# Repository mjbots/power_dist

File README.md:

# mjbots power_dist and mjpower-ss #

This repository contains hardware and firmware for the mjbots
power_dist and mjpower-ss boards.  Both provide pre-charge,
over-current limiting and connector fanout.  The power_dist
additionally provides energy monitoring and a soft-switch
functionality.

# Specifications #

| Name                     | power_dist r4.5b | mjpower-ss r2 |
| ------------------------ |------------------|---------------|
| Voltage Input            | 10-44V           | 10-54V        |
| Current (continous/peak) | 45A/90A          | 45/90A        |
| Output                   | 6x XT30          | 6x XT30       |
| Max load capacitance     | 4000uF           | 4000uF        |
| Quiescent current        | 300uA            | 200uA         |
| Dimensions               | 80x50mm          | 70x50mm       |
| Mass                     | 36g              | 34g           |
| External switch          | X                | X             |
| Soft switch              | X                |               |
| Onboard switch           |                  | X             |
| CAN communication        | X                |               |

# Documentation #

* [Reference](docs/reference.md)

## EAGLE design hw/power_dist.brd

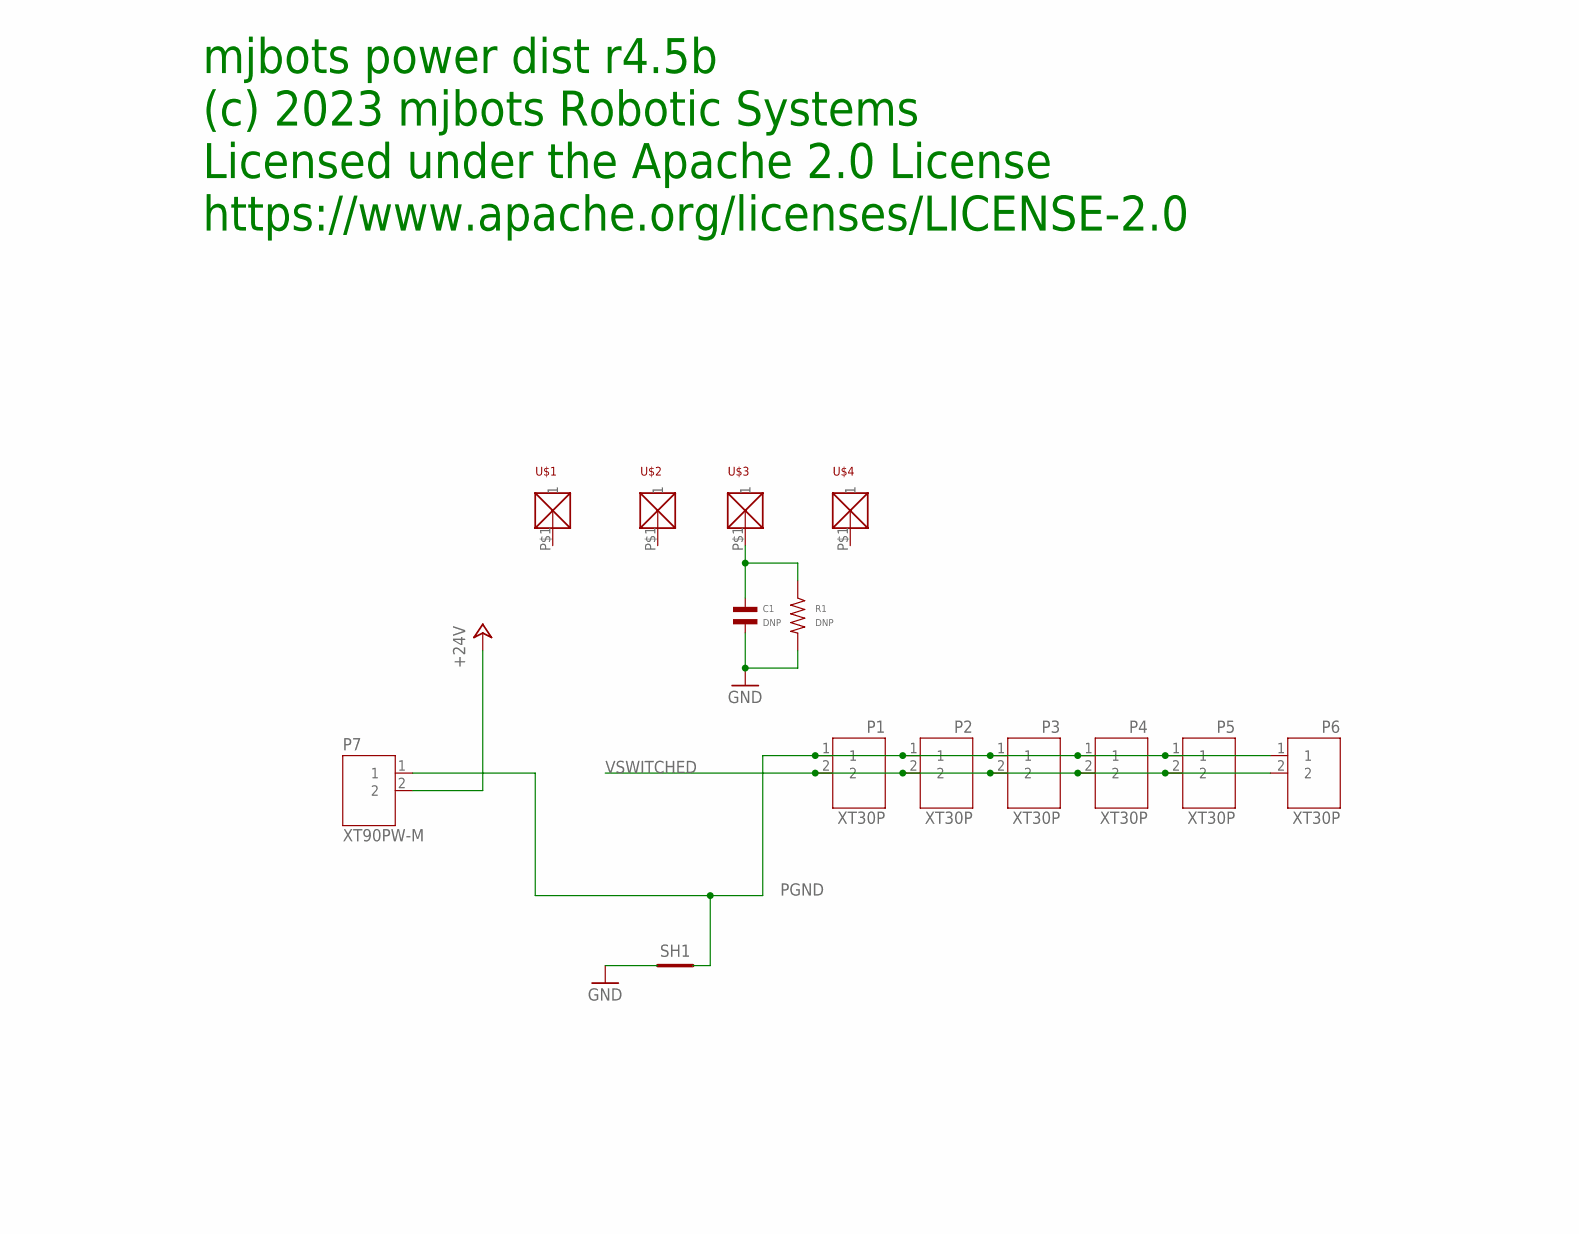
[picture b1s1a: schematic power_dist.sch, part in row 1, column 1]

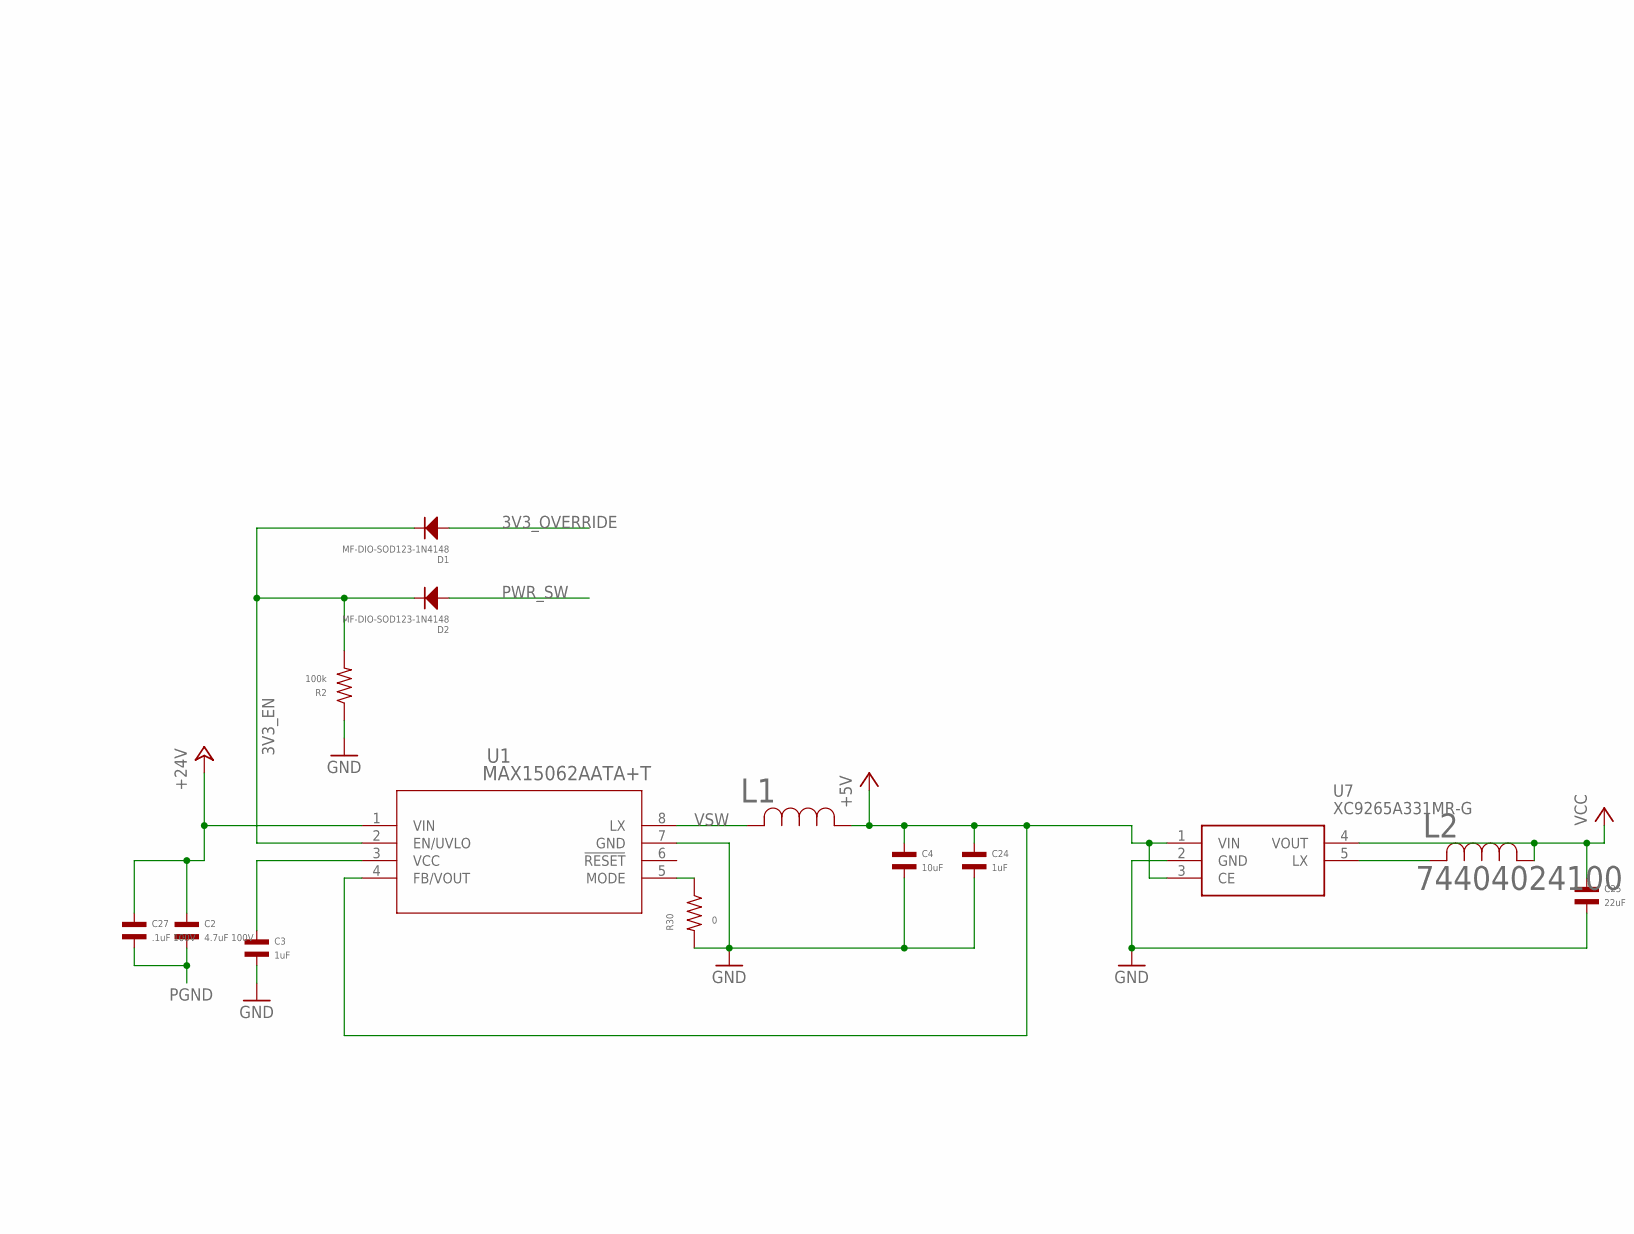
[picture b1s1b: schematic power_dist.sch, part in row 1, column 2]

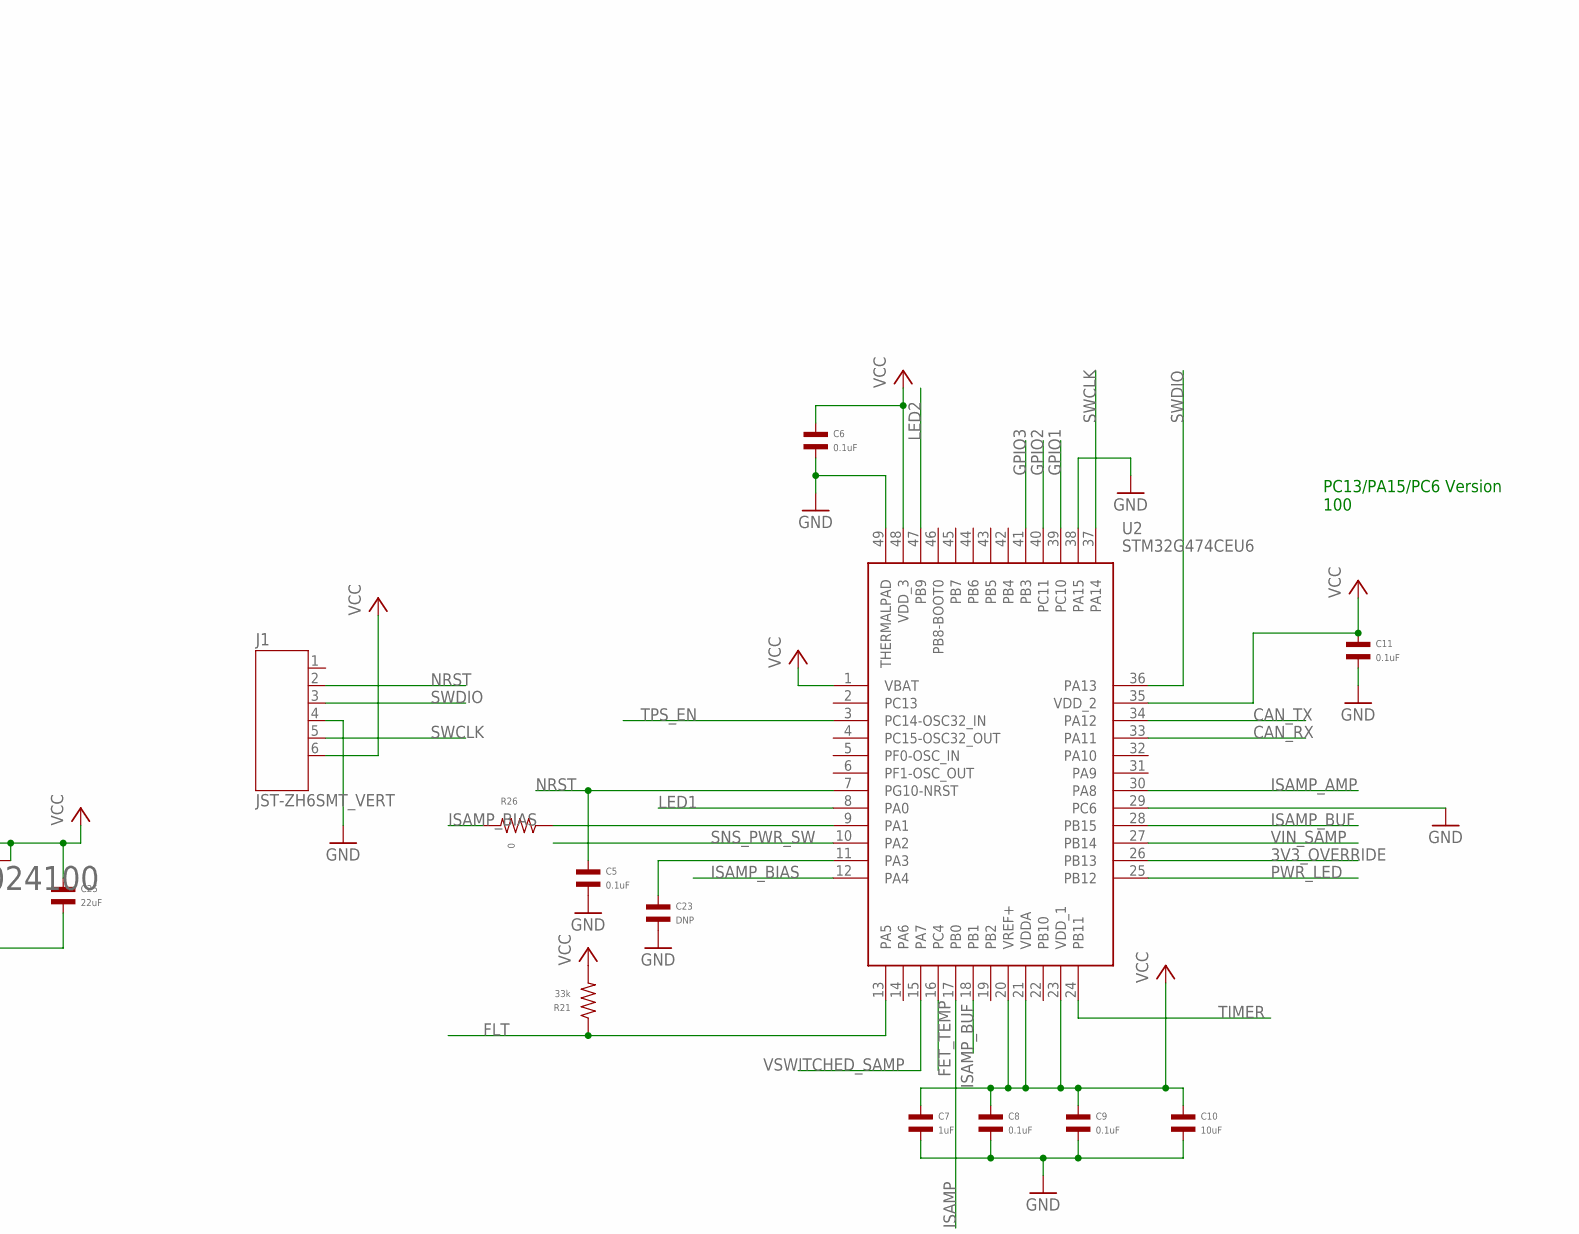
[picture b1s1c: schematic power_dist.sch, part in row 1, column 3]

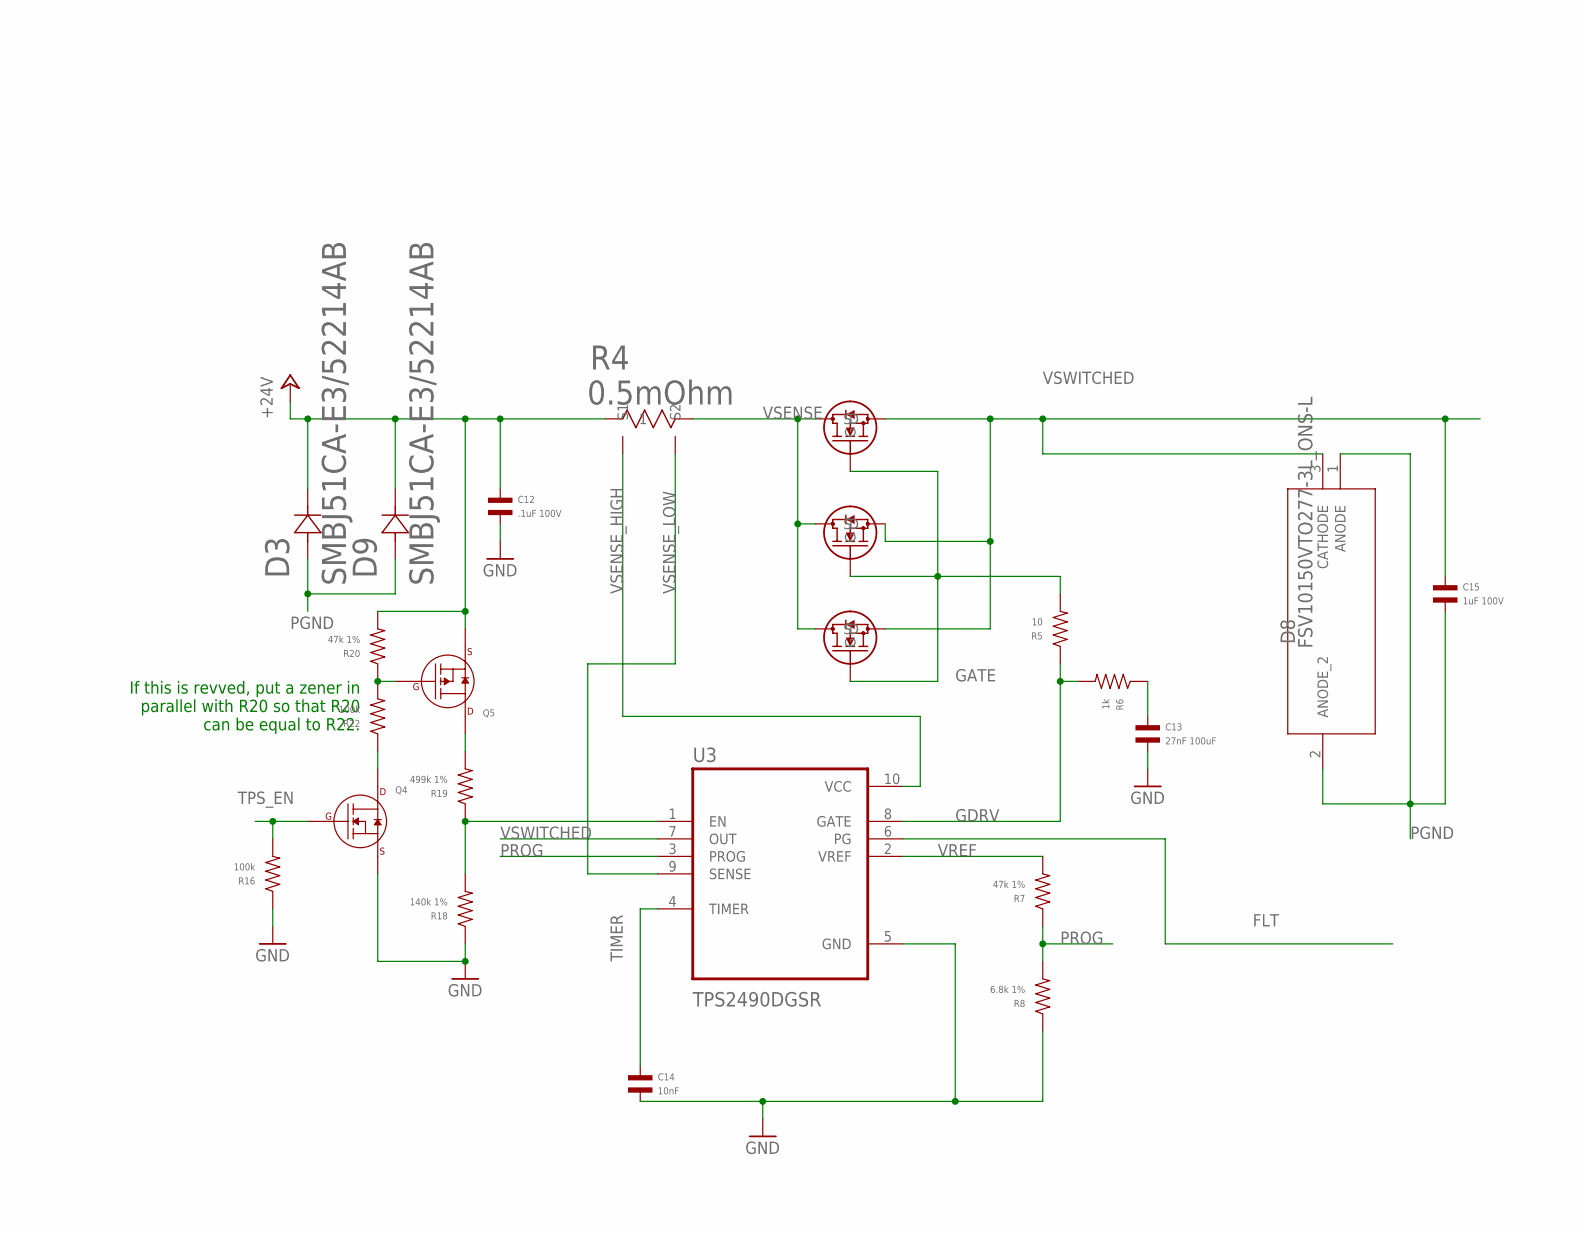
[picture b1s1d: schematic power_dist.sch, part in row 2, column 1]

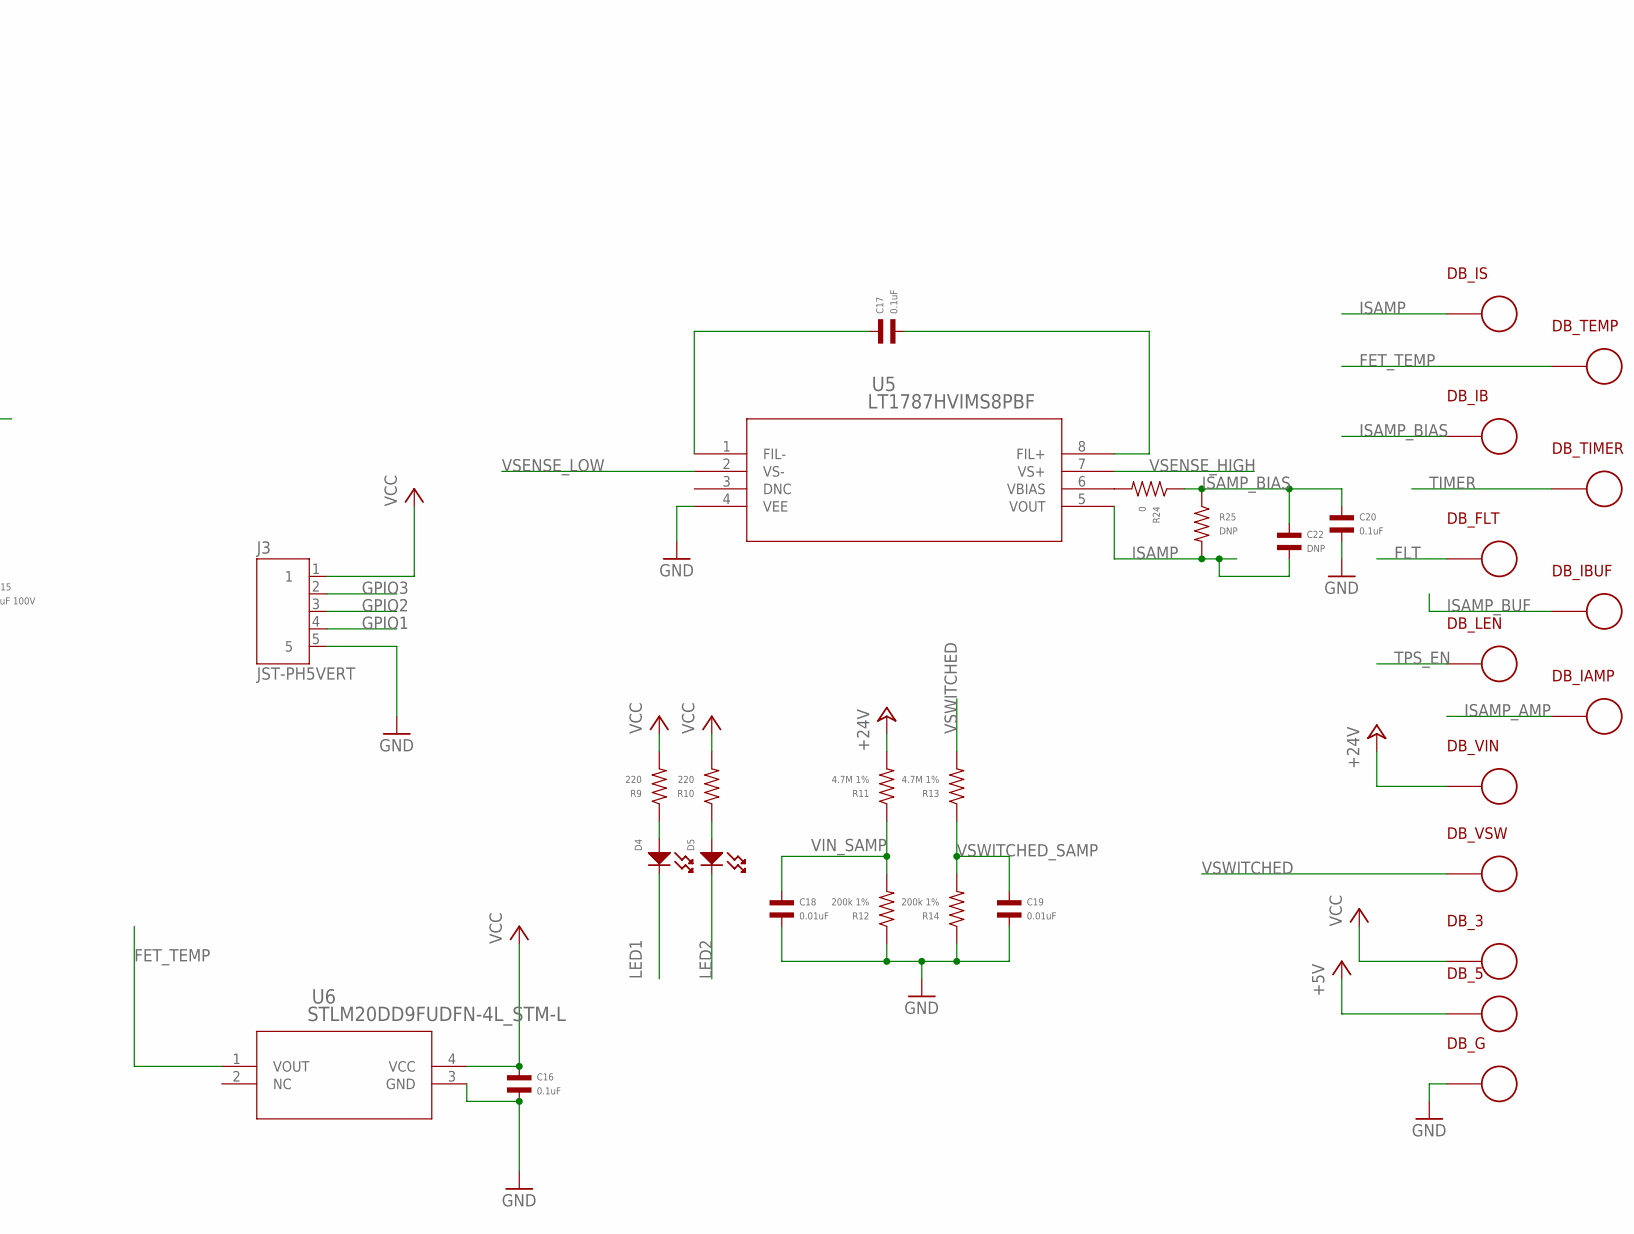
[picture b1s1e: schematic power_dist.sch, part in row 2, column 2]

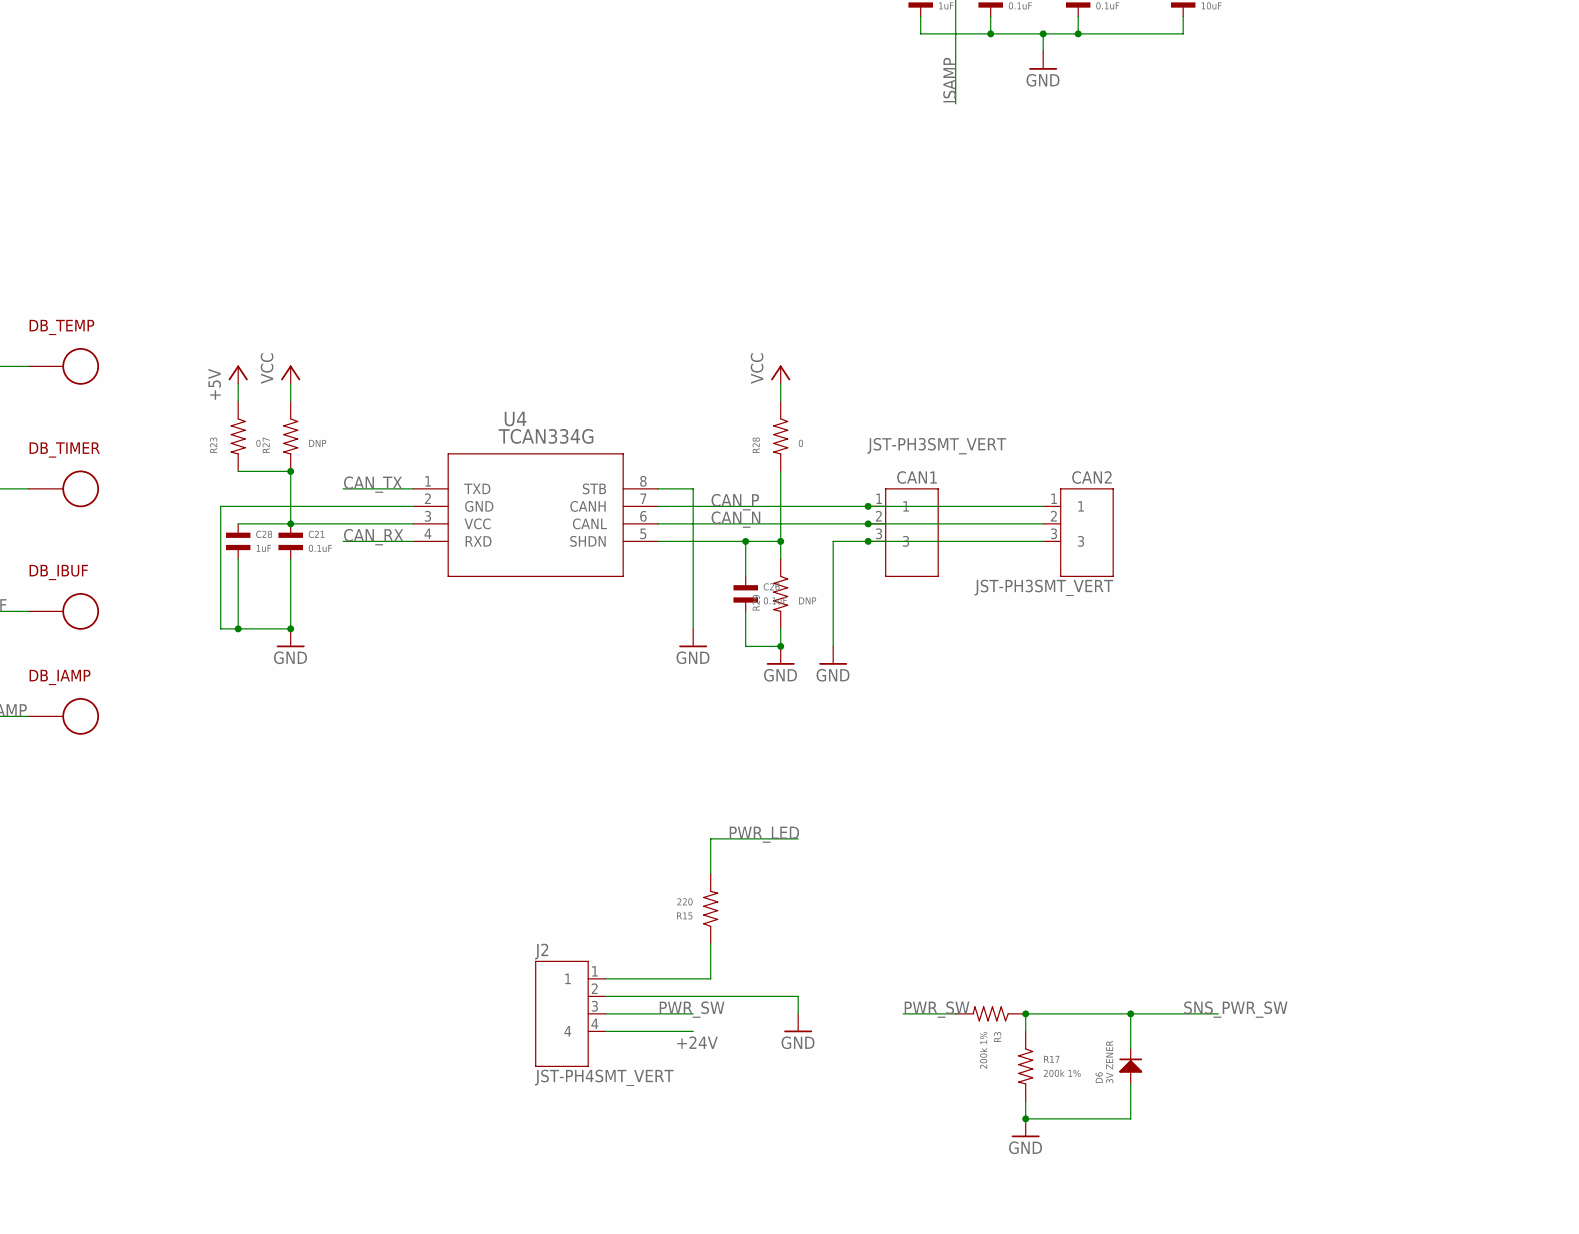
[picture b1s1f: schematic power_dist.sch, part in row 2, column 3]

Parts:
C1, C22, C23: DNP; C0603
C2: 4.7uF 100V; C1206; MPN GRJ31CC72A475KE01K
C3, C7, C28: 1uF; C0603; MPN MF-CAP-0603-1uF
C4, C10: 10uF; C1206; MPN MF-CAP-1206-10uF
C5, C6, C8, C9, C11, C16, C17, C20, C21, C26: 0.1uF; C0603; MPN MF-CAP-0603-0.1uF
C12, C27: .1uF 100V; C0603; MPN GRM188R72A104KA35D
C13: 27nF 100uF; C0603; MPN C0603C273K1RAC7867
C14: 10nF; C0603; MPN MF-CAP-0603-0.01uF
C15: 1uF 100V; C0805; MPN GCM21BC72A105KE36L
C18, C19: 0.01uF; C0603; MPN MF-CAP-0603-0.01uF
C24: 1uF; C0402; MPN MF-CAP-0402-1uF
C25: 22uF; C1206; MPN CL31B226KPHNNNE
CAN1, CAN2: JST-PH3SMT_VERT; JST_B3B_PH-SM4-TB(LF)(SN); MPN B3B-PH-SM4-TB(LF)(SN)
D1, D2: MF-DIO-SOD123-1N4148; SOD-123
D3, D9: SMBJ51CA-E3/52214AB; DIODE_DO-214AB; MPN SMC5K51A-M3/I
D4, D5: LED_SINGLE-0603; LED0603; MPN MF-LED-0603-RED
D6: 3V ZENER; SOD-123; MPN MMSZ4682T1G
D8: FSV10150VTO277-3L_ONS-L; TO277-3L_ONS-L; MPN FSV10150V
DB_3, DB_5: PAD24AWG_PAD; 24AWG_PAD
DB_FLT: PAD24AWG_PAD; 24AWG_PAD
DB_G: PAD24AWG_PAD; 24AWG_PAD
DB_IAMP: PAD24AWG_PAD; 24AWG_PAD
DB_IB: PAD24AWG_PAD; 24AWG_PAD
DB_IBUF: PAD24AWG_PAD; 24AWG_PAD
DB_IS: PAD24AWG_PAD; 24AWG_PAD
DB_LEN: PAD24AWG_PAD; 24AWG_PAD
DB_TEMP: PAD24AWG_PAD; 24AWG_PAD
DB_TIMER: PAD24AWG_PAD; 24AWG_PAD
DB_VIN: PAD24AWG_PAD; 24AWG_PAD
DB_VSW: PAD24AWG_PAD; 24AWG_PAD
J1: JST-ZH6SMT_VERT; JST_B6B-ZR-SM4-TF(LF)(SN); MPN B6B-ZR-SM4-TF(LF)(SN)
J2: JST-PH4SMT_VERT; JST_B4B_PH-SM4-TB(LF)(SN); MPN B4B-PH-SM4-TB(LF)(SN)
J3: JST-PH5VERT; JST_B5B_PH-SM4-TB(LF)(SN); MPN B5B-PH-SM4-TB(LF)(SN)
L1: SRN4018-220M; IND_BOURNS_SRN4018; MANUFACTURER_PART_NUMBER 74404042470
L2: 74404024100; IND_4024100_WRE; MPN MF-RES-0805-0
P1, P2, P3, P4, P5, P6: XT30P; MPN XT30UPB-F
P7: XT90PW-M
Q1, Q2, Q3: PSMN4R8-100BSEJ; D2PAK_SOT404_NEX; MANUFACTURER_PART_NUMBER PSMN3R7-100BSE
Q4: N-CHANNEL_FET_SOT-23-3; SOT-23-3; MPN BSS123
Q5: P-CHANNEL_FET_SOT-23-3; SOT-23-3; MPN ZXMP10A13FTA
R1, R25: DNP; R0603
R2, R16, R22: 100k; R0603; MPN MF-RES-0603-100K
R3, R12, R14, R17: 200k 1%; R0603; MPN RC0603FR-07200KL
R4: 0.5mOhm; SHUNT2512; MPN WSLF2512L5000FEA
R5: 10; R0603; MPN MF-RES-0603-10
R6: 1k; R0603; MPN MF-RES-0603-1K
R7, R20: 47k 1%; R0603; MPN RC0603FR-0747KL
R8: 6.8k 1%; R0603; MPN RC0603FR-076K8L
R9, R10, R15: 220; R0603; MPN MF-RES-0603-220
R11, R13: 4.7M 1%; R0603; MPN RC0603FR-074M7L
R18: 140k 1%; R0603; MPN RC0603FR-07140KL
R19: 499k 1%; R0603; MPN RC0603FR-07499KL
R21: 33k; R0603; MPN RC0603FR-0733KL
R23, R24, R26, R28, R30: 0; R0603; MPN MF-RES-0603-0
R27, R29: DNP; R0603; MPN MF-RES-0603-0
SH1: SHORTMEDIUM; SHORT_TOP-MEDIUM
U1: MAX15062AATA+T; 21-0487A_MXM; MANUFACTURER_PART_NUMBER MAX15062BATA+T
U2: STM32G474CEU6; QFN50P700X700X60-49N; MPN STM32G474CEU6
U3: TPS2490DGSR; SOP50P490X110-10N; MPN TPS2490DGSR
U4: TCAN334G; SOIC8; MPN TCAN1057AEVDRQ1
U5: LT1787HVIMS8PBF; MSOP-8_MS; MPN LT1787HVIMS8
U6: STLM20DD9FUDFN-4L_STM-L; UDFN-4L_STM-L; MPN STLM20DD9F
U7: XC9265A331MR-G; SOT95P280X130-5N; MPN MF-REG-SOT235-3.3V-300mA
U$1, U$2, U$3, U$4: MOUNT; M2.5MOUNT

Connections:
3V3_EN: D1.CATHODE, D2.CATHODE, R2.P$2, U1.2 (EN/UVLO)
3V3_OVERRIDE: D1.ANODE, U2.26 (PB13)
+5V: C4.P$1, C24.P$1, DB_5.P$1, L1.1, R23.P$1, U1.4 (FB/VOUT), U7.1 (VIN), U7.3 (CE)
+24V: C2.P$1, C12.P$1, C27.P$1, D3.P$1 (1), D9.P$1 (1), DB_VIN.P$1, J2.4, P7.2, Q5.P$2 (SOURCE), R4.1, R11.P$2, R20.P$2, U1.1 (VIN)
CAN_N: CAN1.2, CAN2.2, U4.6 (CANL)
CAN_P: CAN1.1, CAN2.1, U4.7 (CANH)
CAN_RX: U2.33 (PA11), U4.4 (RXD)
CAN_TX: U2.34 (PA12), U4.1 (TXD)
FET_TEMP: DB_TEMP.P$1, U2.16 (PC4), U6.1 (VOUT)
FLT: DB_FLT.P$1, R21.P$1, U2.13 (PA5), U3.6 (PG)
GATE: Q1.1 (G), Q2.1 (G), Q3.1 (G), R5.P$2
GDRV: R5.P$1, R6.P$2, U3.8 (GATE)
GND: C1.P$2, C3.P$2, C4.P$2, C5.P$2, C6.P$2, C7.P$2, C8.P$2, C9.P$2, C10.P$2, C11.P$2, C12.P$2, C13.P$2, C14.P$2, C16.P$2, C18.P$2, C19.P$2, C20.P$2, C21.P$2, C23.P$2, C24.P$2, C25.P$2, C26.P$2, C28.P$2, CAN1.3, CAN2.3, D6.ANODE, DB_G.P$1, J1.4, J2.2, J3.5, Q4.P$2 (SOURCE), R1.P$2, R2.P$1, R8.P$1, R12.P$1, R14.P$1, R16.P$1, R17.P$2, R18.P$1, R29.P$2, R30.P$2, SH1.1, U1.7 (GND), U2.29 (PC6), U2.38 (PA15), U2.49 (THERMALPAD), U3.5 (GND), U4.2 (GND), U4.8 (STB), U5.4 (VEE), U6.3 (GND), U7.2 (GND)
GPIO1: J3.4, U2.39 (PC10)
GPIO2: J3.3, U2.40 (PC11)
GPIO3: J3.2, U2.41 (PB3)
ISAMP: C22.P$2, DB_IS.P$1, R25.P$2, U2.17 (PB0), U5.5 (VOUT)
ISAMP_AMP: DB_IAMP.P$1, U2.30 (PA8)
ISAMP_BIAS: C20.P$1, C22.P$1, DB_IB.P$1, R24.P$1, R25.P$1, R26.P$2, U2.12 (PA4)
ISAMP_BUF: DB_IBUF.P$1, U2.18 (PB1), U2.28 (PB15)
LED1: D4.CATHODE, U2.8 (PA0)
LED2: D5.CATHODE, U2.47 (PB9)
unnamed: R30.P$1, U1.5 (MODE)
unnamed: J2.1, R15.P$1
unnamed: R24.P$2, U5.6 (VBIAS)
unnamed: C3.P$1, U1.3 (VCC)
unnamed: C23.P$1, U2.11 (PA3)
unnamed: C17.P$1, U5.1 (FIL-)
unnamed: C17.P$2, U5.8 (FIL+)
unnamed: D4.ANODE, R9.P$1
unnamed: C13.P$1, R6.P$1
unnamed: R26.P$1, U2.9 (PA1)
unnamed: Q5.P$3 (DRAIN), R19.P$2
unnamed: R18.P$2, R19.P$1, U3.1 (EN)
unnamed: Q4.P$3 (DRAIN), R22.P$1
unnamed: D5.ANODE, R10.P$1
unnamed: C1.P$1, R1.P$1, U$3.P$1
unnamed: Q5.P$1 (GATE), R20.P$1, R22.P$2
unnamed: C21.P$1, C28.P$1, R23.P$2, R27.P$2, U4.3 (VCC)
unnamed: L2.2, U7.5 (LX)
unnamed: C26.P$1, R28.P$2, R29.P$1, U4.5 (SHDN)
NRST: C5.P$1, J1.2, U2.7 (PG10-NRST)
PGND: C2.P$2, C15.P$2, C27.P$2, D3.P$2 (2), D8.1 (ANODE), D8.2 (ANODE_2), D9.P$2 (2), P1.1, P2.1, P3.1, P4.1, P5.1, P6.1, P7.1, SH1.2
PROG: R7.P$1, R8.P$2, U3.3 (PROG)
PWR_LED: R15.P$2, U2.25 (PB12)
PWR_SW: D2.ANODE, J2.3, R3.P$2
SNS_PWR_SW: D6.CATHODE, R3.P$1, R17.P$1, U2.10 (PA2)
SWCLK: J1.5, U2.37 (PA14)
SWDIO: J1.3, U2.36 (PA13)
TIMER: C14.P$1, DB_TIMER.P$1, U2.24 (PB11), U3.4 (TIMER)
TPS_EN: DB_LEN.P$1, Q4.P$1 (GATE), R16.P$2, U2.3 (PC14-OSC32_IN)
VCC: C6.P$1, C7.P$1, C8.P$1, C9.P$1, C10.P$1, C11.P$1, C16.P$1, C25.P$1, DB_3.P$1, J1.6, J3.1, L2.1, R9.P$2, R10.P$2, R21.P$2, R27.P$1, R28.P$1, U2.1 (VBAT), U2.20 (VREF+), U2.21 (VDDA), U2.23 (VDD_1), U2.35 (VDD_2), U2.48 (VDD_3), U6.4 (VCC), U7.4 (VOUT)
VIN_SAMP: C18.P$1, R11.P$1, R12.P$2, U2.27 (PB14)
VREF: R7.P$2, U3.2 (VREF)
VSENSE: Q1.2 (D), Q2.2 (D), Q3.2 (D), R4.2
VSENSE_HIGH: R4.3 (S1), U3.10 (VCC), U5.7 (VS+)
VSENSE_LOW: R4.4 (S2), U3.9 (SENSE), U5.2 (VS-)
VSW: L1.2, U1.8 (LX)
VSWITCHED: C15.P$1, D8.3 (CATHODE), DB_VSW.P$1, P1.2, P2.2, P3.2, P4.2, P5.2, P6.2, Q1.3 (S), Q2.3 (S), Q3.3 (S), R13.P$2, U3.7 (OUT)
VSWITCHED_SAMP: C19.P$1, R13.P$1, R14.P$2, U2.15 (PA7)

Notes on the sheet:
mjbots power dist r4.5b (c) 2023 mjbots Robotic Systems Licensed under the Apache 2.0 License https://www.apache.org/licenses/LICENSE-2.0
PC13/PA15/PC6 Version 100
If this is revved, put a zener in parallel with R20 so that R20 can be equal to R22.

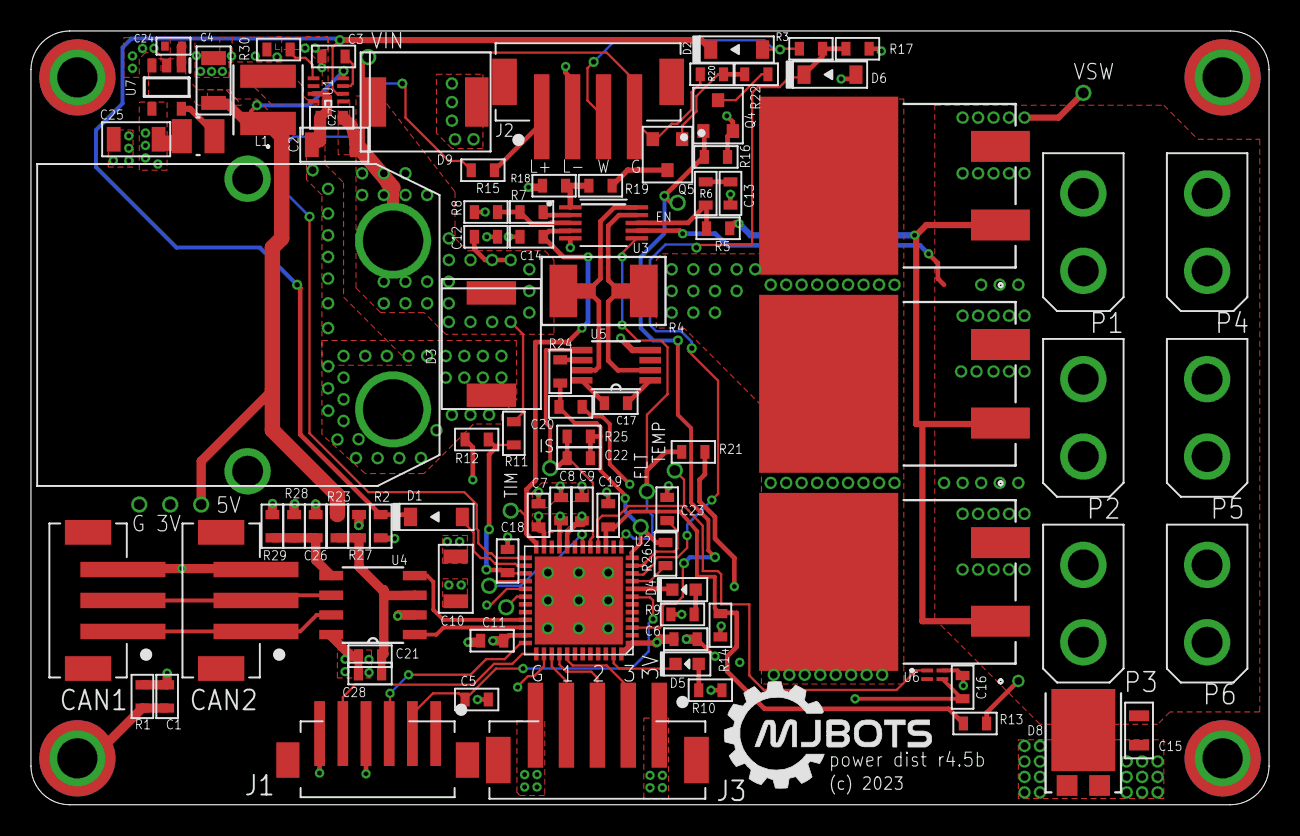
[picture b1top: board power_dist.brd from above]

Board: 4 copper layers, 80.0 x 50.0 mm, 110 parts (0 on the bottom side), 60 nets.

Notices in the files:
hw/r3.1/power_dist.sch:
(c) 2020 Josh Pieper, jjp@pobox.com
parts and their libraries:
COPYRIGHT: Copyright (C) 2018 Accelerated Designs. All rights reserved
moteus_hp: COPYRIGHT: Copyright (C) 2022 Ultra Librarian. All rights reserved.
